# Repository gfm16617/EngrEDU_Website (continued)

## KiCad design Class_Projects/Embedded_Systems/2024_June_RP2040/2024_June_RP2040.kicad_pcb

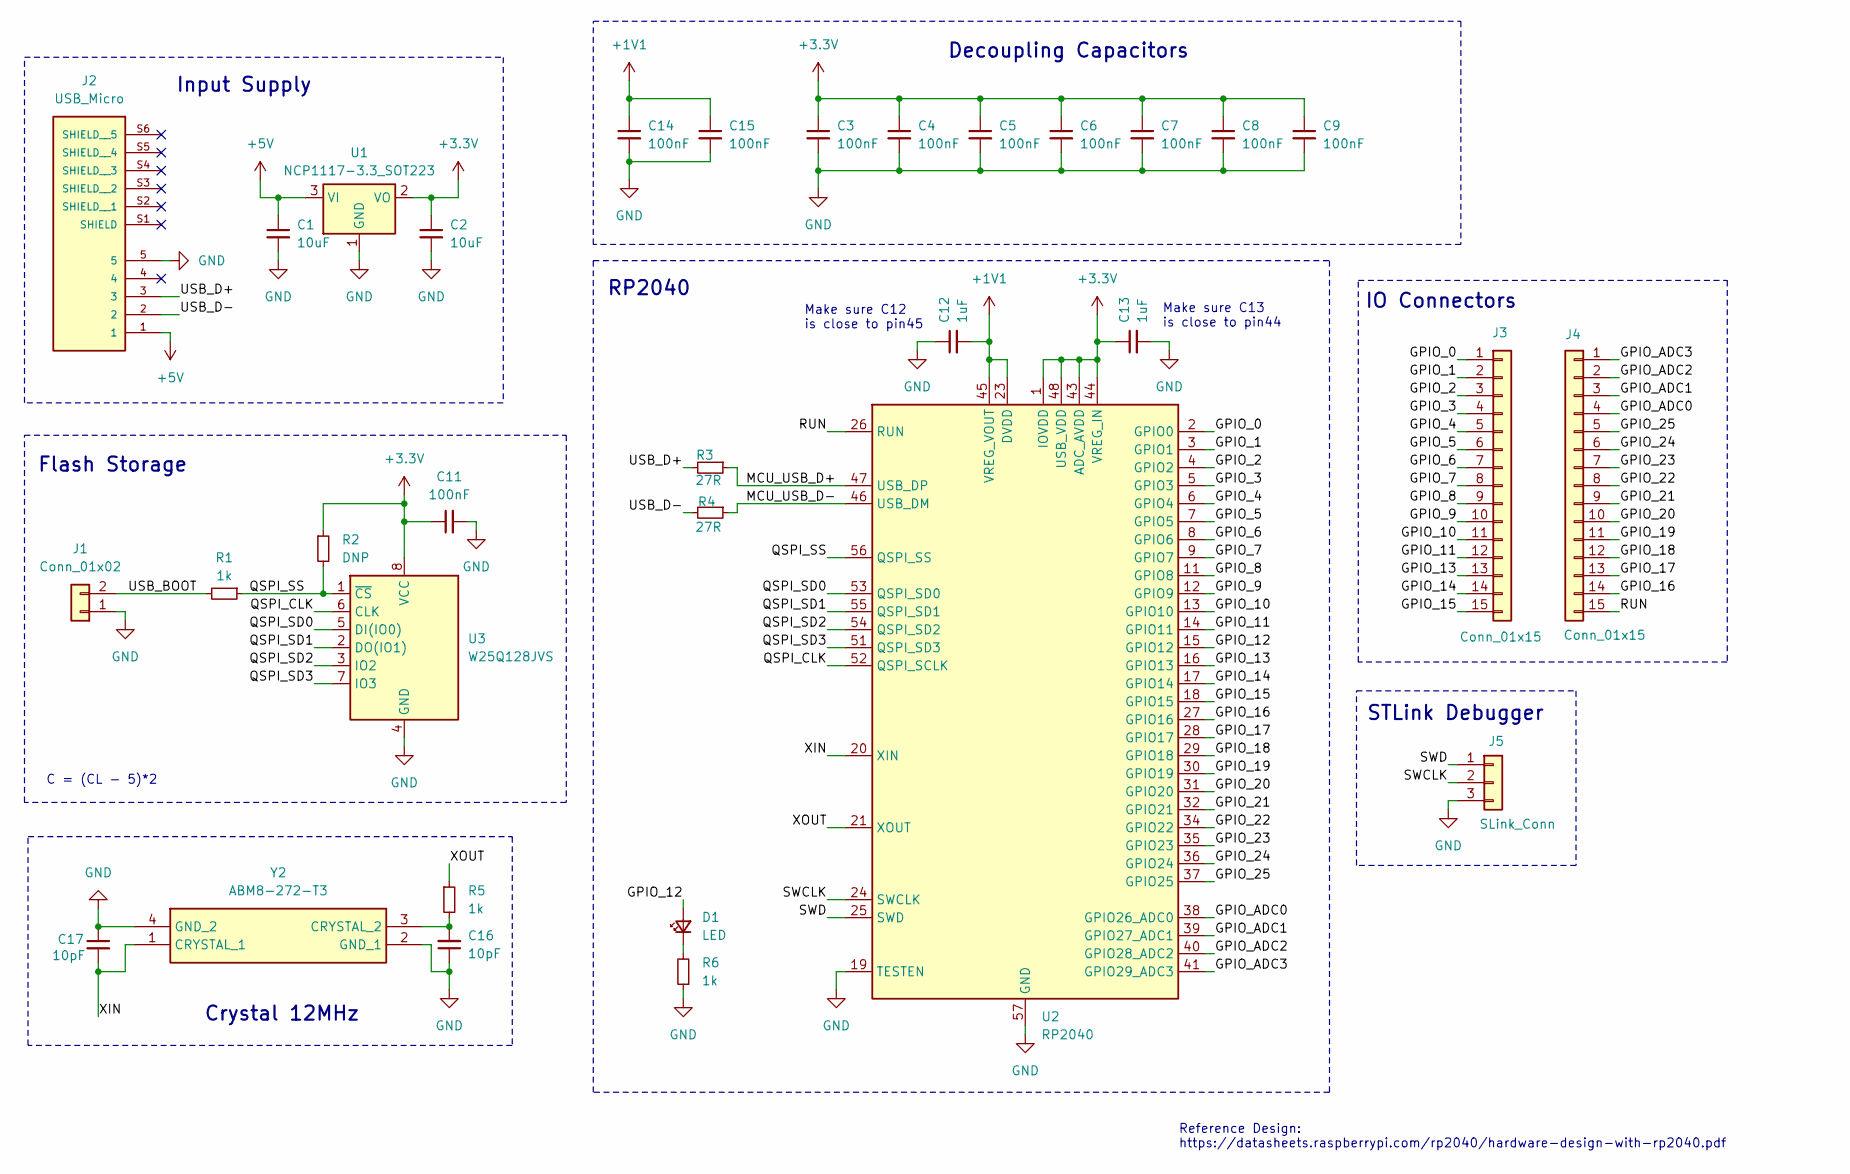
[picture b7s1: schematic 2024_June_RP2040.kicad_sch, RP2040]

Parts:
C1, C2: 10uF; C_0805_2012Metric_Pad1.18x1.45mm_HandSolder
C3, C4, C5, C6, C7, C8, C9, C11, C14, C15: 100nF; C_0402_1005Metric_Pad0.74x0.62mm_HandSolder
C12, C13: 1uF; C_0402_1005Metric_Pad0.74x0.62mm_HandSolder
C16, C17: 10pF; C_0402_1005Metric_Pad0.74x0.62mm_HandSolder
D1: LED; LED_0402_1005Metric_Pad0.77x0.64mm_HandSolder
J1: Conn_01x02; PinHeader_1x02_P2.54mm_Vertical
J2: USB_Micro; USB_B_Micro_Amphenol; PARTREV D
J3, J4: Conn_01x15; PinHeader_1x15_P2.54mm_Vertical
J5: SLink_Conn; PinHeader_1x03_P2.54mm_Vertical
R1, R5, R6: 1k; R_0402_1005Metric_Pad0.72x0.64mm_HandSolder
R2: DNP; R_0402_1005Metric_Pad0.72x0.64mm_HandSolder
R3, R4: 27R; R_0402_1005Metric_Pad0.72x0.64mm_HandSolder
U1: NCP1117-3.3_SOT223; SOT-223-3_TabPin2
U2: RP2040; QFN-56-1EP_7x7mm_P0.4mm_EP3.2x3.2mm
U3: W25Q128JVS; SOIC-8_5.23x5.23mm_P1.27mm
Y2: ABM8-272-T3; Crytal_ABM8-272-T3; Manufacturer_Part_Number ABM8-272-T3; Mouser Part Number 815-ABM8-272-T3

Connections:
+1V1: C12.2, C14.1, C15.1, U2.23 (DVDD), U2.45 (VREG_VOUT), U2.50 (DVDD)
+3.3V: C2.1, C3.1, C4.1, C5.1, C6.1, C7.1, C8.1, C9.1, C11.1, C13.1, R2.1, U1.2 (VO), U2.1 (IOVDD), U2.10 (IOVDD), U2.22 (IOVDD), U2.33 (IOVDD), U2.42 (IOVDD), U2.43 (ADC_AVDD), U2.44 (VREG_IN), U2.48 (USB_VDD), U2.49 (IOVDD), U3.8 (VCC)
+5V: C1.1, J2.1, U1.3 (VI)
/GPIO_0: J3.1, U2.2 (GPIO0)
/GPIO_1: J3.2, U2.3 (GPIO1)
/GPIO_2: J3.3, U2.4 (GPIO2)
/GPIO_3: J3.4, U2.5 (GPIO3)
/GPIO_4: J3.5, U2.6 (GPIO4)
/GPIO_5: J3.6, U2.7 (GPIO5)
/GPIO_6: J3.7, U2.8 (GPIO6)
/GPIO_7: J3.8, U2.9 (GPIO7)
/GPIO_8: J3.9, U2.11 (GPIO8)
/GPIO_9: J3.10, U2.12 (GPIO9)
/GPIO_10: J3.11, U2.13 (GPIO10)
/GPIO_11: J3.12, U2.14 (GPIO11)
/GPIO_12: D1.2 (A), U2.15 (GPIO12)
/GPIO_13: J3.13, U2.16 (GPIO13)
/GPIO_14: J3.14, U2.17 (GPIO14)
/GPIO_15: J3.15, U2.18 (GPIO15)
/GPIO_16: J4.14, U2.27 (GPIO16)
/GPIO_17: J4.13, U2.28 (GPIO17)
/GPIO_18: J4.12, U2.29 (GPIO18)
/GPIO_19: J4.11, U2.30 (GPIO19)
/GPIO_20: J4.10, U2.31 (GPIO20)
/GPIO_21: J4.9, U2.32 (GPIO21)
/GPIO_22: J4.8, U2.34 (GPIO22)
/GPIO_23: J4.7, U2.35 (GPIO23)
/GPIO_24: J4.6, U2.36 (GPIO24)
/GPIO_25: J4.5, U2.37 (GPIO25)
/GPIO_ADC0: J4.4, U2.38 (GPIO26_ADC0)
/GPIO_ADC1: J4.3, U2.39 (GPIO27_ADC1)
/GPIO_ADC2: J4.2, U2.40 (GPIO28_ADC2)
/GPIO_ADC3: J4.1, U2.41 (GPIO29_ADC3)
/MCU_USB_D+: R3.1, U2.47 (USB_DP)
/MCU_USB_D-: R4.1, U2.46 (USB_DM)
/QSPI_CLK: U2.52 (QSPI_SCLK), U3.6 (CLK)
/QSPI_SD0: U2.53 (QSPI_SD0), U3.5 (DI(IO0))
/QSPI_SD1: U2.55 (QSPI_SD1), U3.2 (DO(IO1))
/QSPI_SD2: U2.54 (QSPI_SD2), U3.3 (IO2)
/QSPI_SD3: U2.51 (QSPI_SD3), U3.7 (IO3)
/QSPI_SS: R1.1, R2.2, U2.56 (QSPI_SS), U3.1 (~CS)
/RUN: J4.15, U2.26 (RUN)
/SWCLK: J5.2, U2.24 (SWCLK)
/SWD: J5.1, U2.25 (SWD)
/USB_BOOT: J1.2, R1.2
/USB_D+: J2.3, R3.2
/USB_D-: J2.2, R4.2
/XIN: C17.2, U2.20 (XIN), Y2.1 (CRYSTAL_1)
/XOUT: R5.1, U2.21 (XOUT)
GND: C1.2, C2.2, C3.2, C4.2, C5.2, C6.2, C7.2, C8.2, C9.2, C11.2, C12.1, C13.2, C14.2, C15.2, C16.1, C17.1, J1.1, J2.5, J5.3, R6.1, U1.1 (GND), U2.19 (TESTEN), U2.57 (GND), U3.4 (GND), Y2.2 (GND_1), Y2.4 (GND_2)
unnamed: D1.1 (K), R6.2
unnamed: C16.2, R5.2, Y2.3 (CRYSTAL_2)

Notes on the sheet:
Make sure C12 is close to pin45
Crystal 12MHz
STLink Debugger
C = (CL - 5)*2
Flash Storage
IO Connectors
RP2040
Decoupling Capacitors
Input Supply
Make sure C13 is close to pin44
Reference Design: https://datasheets.raspberrypi.com/rp2040/hardware-design-with-rp2040.pdf

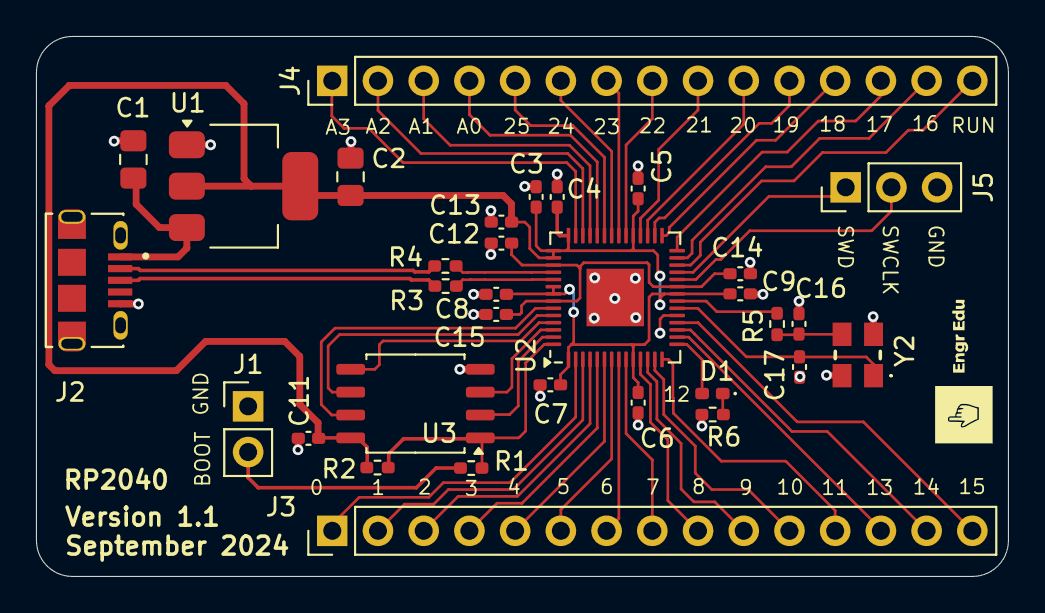
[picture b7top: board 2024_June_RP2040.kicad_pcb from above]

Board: 2 copper layers, 54.0 x 30.0 mm, 32 parts (0 on the bottom side), 52 nets.

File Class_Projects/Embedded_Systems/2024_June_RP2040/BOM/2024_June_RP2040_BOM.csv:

Item,Ref Des,Qty,Manufacturer,Description / Value,Package,Type
1,"C3, C4, C5, C6, C7, C8, C9, C11, C14, C15",10,0402YC104KAT2A,100nF,C_0402_1005Metric_Pad0.74x0.62mm_HandSolder,SMD
2,"C1, C2",2,0805YC106KAT2A,10uF,C_0805_2012Metric_Pad1.18x1.45mm_HandSolder,SMD
3,"C12, C13",2,C0402C105K9PAC,1uF,C_0402_1005Metric_Pad0.74x0.62mm_HandSolder,SMD
4,"C16, C17",2,C0402C100J3GACAUTO,10pF,C_0402_1005Metric_Pad0.74x0.62mm_HandSolder,SMD
5,"R1, R5, R6",3,CRT0402-BY-1001GLF,1k,R_0402_1005Metric_Pad0.72x0.64mm_HandSolder,SMD
6,"R3, R4",2,RCS040227R0FKED,27R,R_0402_1005Metric_Pad0.72x0.64mm_HandSolder,SMD
7,R2,1,,DNP,R_0402_1005Metric_Pad0.72x0.64mm_HandSolder,DNP
8,D1,1,IN-S42BTR,LED,LED_0402_1005Metric_Pad0.77x0.64mm_HandSolder,SMD
9,U1,1,NCP1117IST33T3G,NCP1117-3.3_SOT223,SOT-223-3_TabPin2,SMD
10,U2,1,SC0914(7),RP2040,QFN-56-1EP_7x7mm_P0.4mm_EP3.2x3.2mm,SMD
11,U3,1,W25Q128JVSIM,W25Q128JVS,SOIC-8_5.23x5.23mm_P1.27mm,SMD
12,Y2,1,ABM8-272-T3,ABM8-272-T3,Crytal_ABM8-272-T3,SMD
13,"J3, J4",2,,Conn_01x15,PinHeader_1x15_P2.54mm_Vertical,DNP
14,J1,1,,Conn_01x02,PinHeader_1x02_P2.54mm_Vertical,DNP
15,J2,1,10118194-0001LF,USB_Micro,USB_B_Micro_Amphenol,SMD
16,J5,1,,SLink_Conn,PinHeader_1x03_P2.54mm_Vertical,DNP
